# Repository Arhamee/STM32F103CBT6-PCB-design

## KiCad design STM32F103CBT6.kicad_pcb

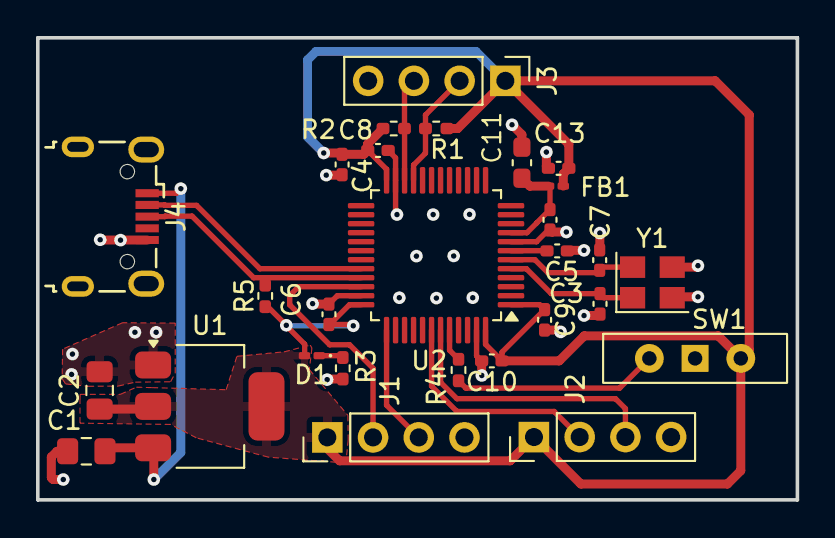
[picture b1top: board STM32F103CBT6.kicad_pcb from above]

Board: 2 copper layers, 42.2 x 25.7 mm, 28 parts (0 on the bottom side), 18 nets.

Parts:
C1, C2: 22u; C_0805_2012Metric_Pad1.18x1.45mm_HandSolder
C3, C7: 10p; C_0402_1005Metric_Pad0.74x0.62mm_HandSolder
C4: 10u; C_0402_1005Metric_Pad0.74x0.62mm_HandSolder
C5, C6, C8, C9, C10: 100n; C_0402_1005Metric_Pad0.74x0.62mm_HandSolder
C11: 10u; C_0603_1608Metric_Pad1.08x0.95mm_HandSolder
C12, C13: 1u; C_0402_1005Metric_Pad0.74x0.62mm_HandSolder
D1: LED; LED_0201_0603Metric_Pad0.64x0.40mm_HandSolder
FB1: FerriteBead; L_0201_0603Metric_Pad0.64x0.40mm_HandSolder
J1, J2, J3: Conn_01x04_Pin; PinHeader_1x04_P2.54mm_Vertical
J4: USB_B_Micro; USB_Micro-B_Wuerth_629105150521
R1, R2, R3, R5: 1k5; R_0402_1005Metric_Pad0.72x0.64mm_HandSolder
R4: 10k; R_0402_1005Metric_Pad0.72x0.64mm_HandSolder
SW1: SW_SPDT; SW_Slide-03_Wuerth-WS-SLTV_10x2.5x6.4_P2.54mm
U1: AMS1117-3.3; SOT-223-3_TabPin2
U2: STM32F103CBTx; LQFP-48_7x7mm_P0.5mm
Y1: Crystal_GND23; Crystal_SMD_3225-4Pin_3.2x2.5mm

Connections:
+3.3V: C2.1, C4.1, C6.1, C8.1, C9.1, C10.1, C13.1, D1.2 (A), FB1.2, J1.1, J2.1, J3.1, R1.1, R2.1, R5.1, SW1.3 (C), U1.2 (VO), U2.1 (VBAT), U2.24 (VDD), U2.36 (VDD), U2.48 (VDD)
+3.3VA: C11.1, C12.1, FB1.1, U2.9 (VDDA)
/HSE_IN: C3.1, U2.5 (PD0), Y1.1
/HSE_OUT: C7.1, U2.6 (PD1), Y1.4
/RX: J2.3, U2.43 (PB7)
/SCL: J3.2, R1.2, U2.21 (PB10)
/SDA: J3.3, R2.2, U2.22 (PB11)
/SWCLK: J1.3, U2.37 (PA14)
/SWOIO: J1.2, U2.34 (PA13)
/TX: J2.2, U2.42 (PB6)
/USB_D+: J4.3 (D+), R5.2, U2.33 (PA12)
/USB_D-: J4.2 (D-), U2.32 (PA11)
GND: C1.2, C2.2, C3.2, C4.2, C5.2, C6.2, C7.2, C8.2, C9.2, C10.2, C11.2, C12.2, C13.2, J1.4, J2.4, J3.4, J4.5 (GND), R3.1, SW1.1 (A), U1.1 (GND), U2.8 (VSSA), U2.23 (VSS), U2.35 (VSS), U2.47 (VSS), Y1.2, Y1.3
unnamed: D1.1 (K), R3.2
unnamed: R4.1, SW1.2 (B)
unnamed: R4.2, U2.44 (BOOT0)
unnamed: C5.1, U2.7 (NRST)
VBUS: C1.1, J4.1 (VBUS), U1.3 (VI)
